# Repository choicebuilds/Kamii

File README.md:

# SumoBot v2
A significantly improved version of [SumoBot v1](https://github.com/choicebuilds/SumoBot-v1)!  Concise documentation intended as a project showcase for my portfolio/resume.
  
Notable Improvements:
- 4-layer PCB with dedicated 9V/5V planes and a solid ground plane to improve return current paths and help reduce EMI
- Decoupling & bulk capacitors placed throughout the board for improved power integrity
- STM32 MCU + STM32CubeMX + C/Cmake Firmware
- Various quality of life additions (e.g. strategy switch, remote start, on/off switch, etc.)
- Compact layout featuring 0402 surface-mount components (ft. dog-bone fanout for motor drivers for space and cost)
 
## Hardware Showcase

## Soldering Showcase
With the JLCPCB Stencil: $14.16 (PCB) + $21.69 (Shipping) - $5 (Coupon) = $30.85 + Tax  
Without the JLCPCB Stencil: $7 (PCB) + $3.12 (Shipping) - $5 (Coupon) = $5.12 + Tax  
I went with the second option and generated a stencil using the LPKF Protolaser.  
   
I would not recommend, especially for a small PCB, because the stencil did not sit flat. Required a few manual adjustments.  
  
Then, a reflow oven was used for SMD components:  
   
And the remaining components were through-hole soldered.

## WARNING
I flipped the polarity of the XT-30 connector on the silkscreen without reverse-polarity protection:  
  
It made a very loud sound when the bulk capacitor blew up. Lesson learned to always double check.

## Demo Video

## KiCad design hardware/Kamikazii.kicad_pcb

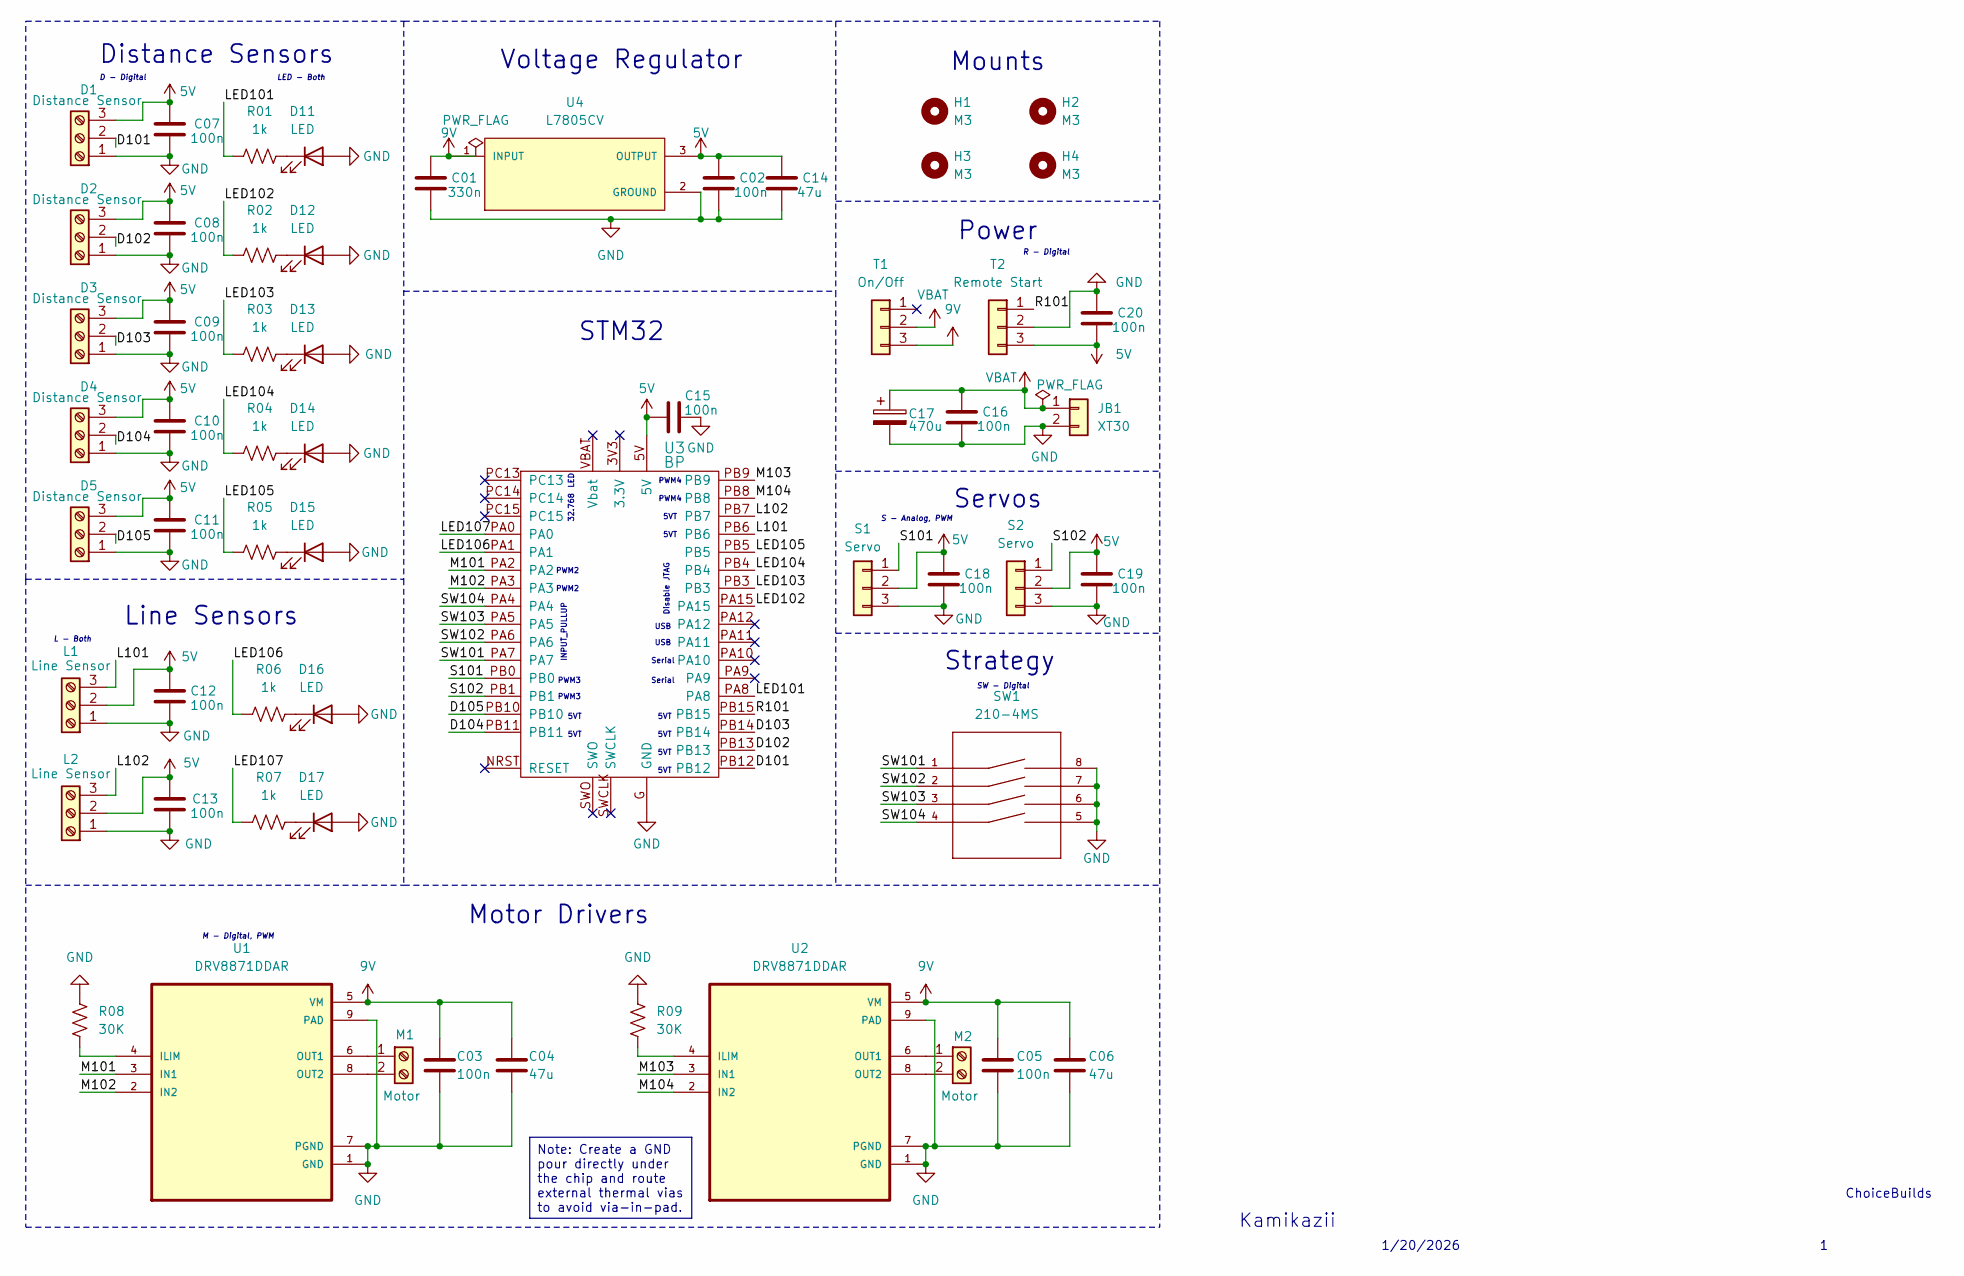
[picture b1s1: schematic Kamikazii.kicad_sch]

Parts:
C01: 330n; C_0402_1005Metric
C02, C03, C05, C07, C08, C09, C10, C11, C12, C13, C15, C16, C18, C19, C20: 100n; C_0402_1005Metric
C04, C06, C14: 47u; C_1210_3225Metric
C17: 470u; CP_Radial_D8.0mm_P3.50mm
D1, D2, D3, D4, D5: Distance Sensor; TerminalBlock_Xinya_XY308-2.54-3P_1x03_P2.54mm_Horizontal
D11, D12, D13, D14, D15, D16, D17: LED; LED_0402_1005Metric
H1, H2, H3, H4: M3; MountingHole_3.2mm_M3
JB1: XT30; AMASS_XT30U-F_1x02_P5.0mm_Vertical
L1, L2: Line Sensor; TerminalBlock_Xinya_XY308-2.54-3P_1x03_P2.54mm_Horizontal
M1, M2: Motor; TerminalBlock_Xinya_XY308-2.54-2P_1x02_P2.54mm_Horizontal
R01, R02, R03, R04, R05, R06, R07: 1k; R_0402_1005Metric
R08, R09: 30K; R_0402_1005Metric
S1, S2: Servo; PinHeader_1x03_P2.54mm_Vertical
SW1: 210-4MS; MANUFACTURER_PART_NUMBER 210-4MS
T1: On/Off; PinHeader_1x03_P2.54mm_Vertical
T2: Remote Start; PinHeader_1x03_P2.54mm_Vertical
U1, U2: DRV8871DDAR; VREG_LM5017MR_NOPB
U3: BP; blue_pill
U4: L7805CV; TO255P1040X460X1968-3; PARTREV 36

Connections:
5V: C02.2, C07.1, C08.1, C09.1, C10.1, C11.1, C12.1, C13.1, C14.2, C15.1, C18.2, C19.2, C20.1, D1.3, D2.3, D3.3, D4.3, D5.3, L1.2, L2.2, S1.2, S2.2, T2.3, U3.5V, U4.3 (OUTPUT)
9V: C01.2, C03.1, C04.1, C05.1, C06.1, T1.3, U1.5 (VM), U2.5 (VM), U4.1 (INPUT)
/D101: D1.2, U3.PB12
/D102: D2.2, U3.PB13
/D103: D3.2, U3.PB14
/D104: D4.2, U3.PB11
/D105: D5.2, U3.PB10
/L101: L1.3, U3.PB6
/L102: L2.3, U3.PB7
/LED101: R01.1, U3.PA8
/LED102: R02.1, U3.PA15
/LED103: R03.1, U3.PB3
/LED104: R04.1, U3.PB4
/LED105: R05.1, U3.PB5
/LED106: R06.1, U3.PA1
/LED107: R07.1, U3.PA0
/M101: U1.3 (IN1), U3.PA2
/M102: U1.2 (IN2), U3.PA3
/M103: U2.3 (IN1), U3.PB9
/M104: U2.2 (IN2), U3.PB8
/R101: T2.1, U3.PB15
/S101: S1.1, U3.PB0
/S102: S2.1, U3.PB1
/SW101: SW1.1, U3.PA7
/SW102: SW1.2, U3.PA6
/SW103: SW1.3, U3.PA5
/SW104: SW1.4, U3.PA4
GND: C01.1, C02.1, C03.2, C04.2, C05.2, C06.2, C07.2, C08.2, C09.2, C10.2, C11.2, C12.2, C13.2, C14.1, C15.2, C16.1, C17.2, C18.1, C19.1, C20.2, D1.1, D2.1, D3.1, D4.1, D5.1, D11.2 (A), D12.2 (A), D13.2 (A), D14.2 (A), D15.2 (A), D16.2 (A), D17.2 (A), JB1.2, L1.1, L2.1, R08.1, R09.1, S1.3, S2.3, SW1.5, SW1.6, SW1.7, SW1.8, T2.2, U1.1 (GND), U1.7 (PGND), U1.9 (PAD), U2.1 (GND), U2.7 (PGND), U2.9 (PAD), U3.G (GND), U4.2 (GROUND)
unnamed: D11.1 (K), R01.2
unnamed: D12.1 (K), R02.2
unnamed: D13.1 (K), R03.2
unnamed: D14.1 (K), R04.2
unnamed: D15.1 (K), R05.2
unnamed: D16.1 (K), R06.2
unnamed: D17.1 (K), R07.2
unnamed: M1.1, U1.6 (OUT1)
unnamed: M1.2, U1.8 (OUT2)
unnamed: M2.1, U2.6 (OUT1)
unnamed: M2.2, U2.8 (OUT2)
unnamed: R08.2, U1.4 (ILIM)
unnamed: R09.2, U2.4 (ILIM)
VBAT: C16.2, C17.1, JB1.1, T1.2

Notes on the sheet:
Power
Motor Drivers
INPUT_PULLUP
PWM3
32.768
5VT
PWM2
S - Analog, PWM
D - Digital
Kamikazii
L - Both
LED - Both
1/20/2026
Serial
PWM4
ChoiceBuilds
Mounts
SW - Digital
LED
R - Digital
Voltage Regulator
Servos
Line Sensors
Strategy
USB
Disable JTAG
STM32
Distance Sensors
M - Digital, PWM
Note: Create a GND pour directly under the chip and route external thermal vias to avoid via-in-pad.

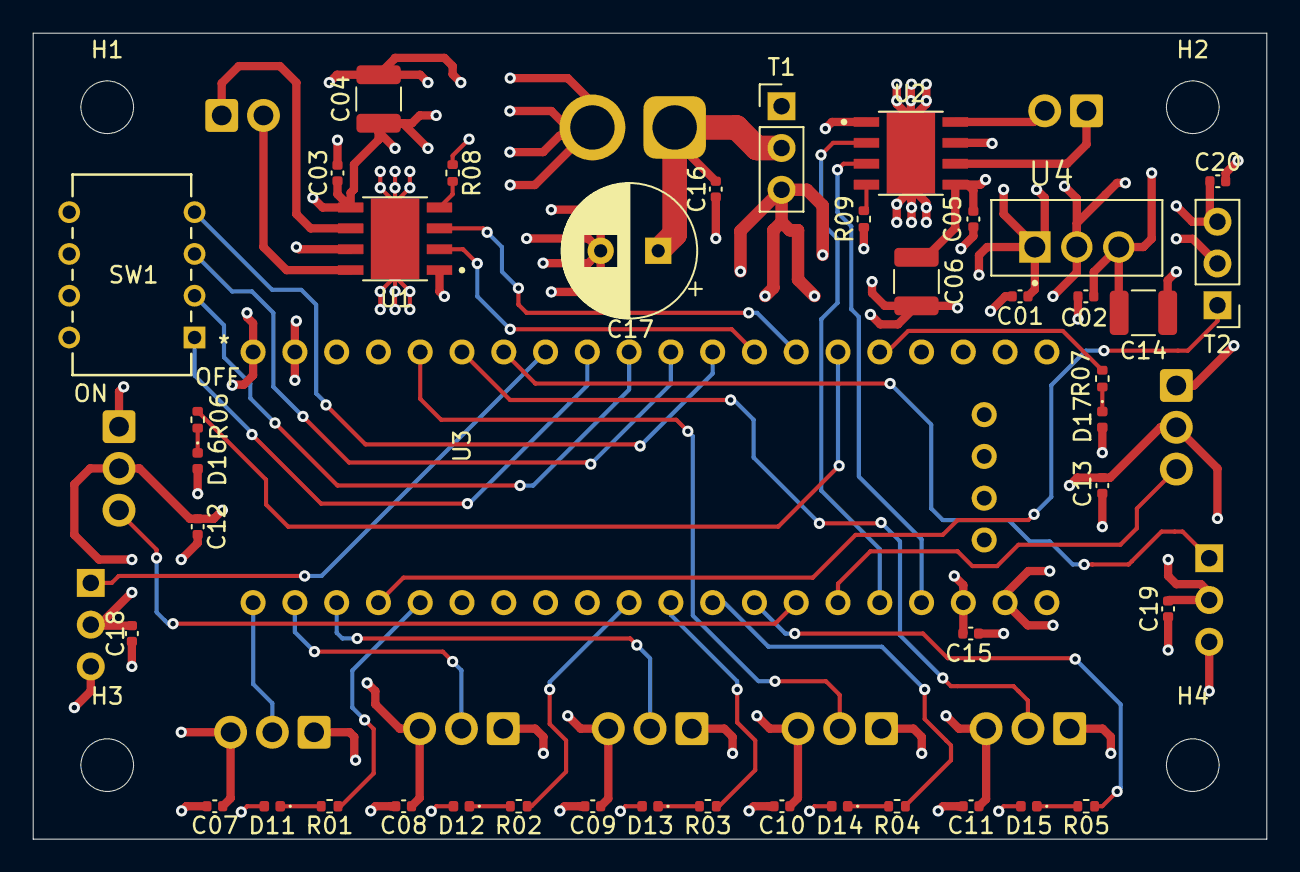
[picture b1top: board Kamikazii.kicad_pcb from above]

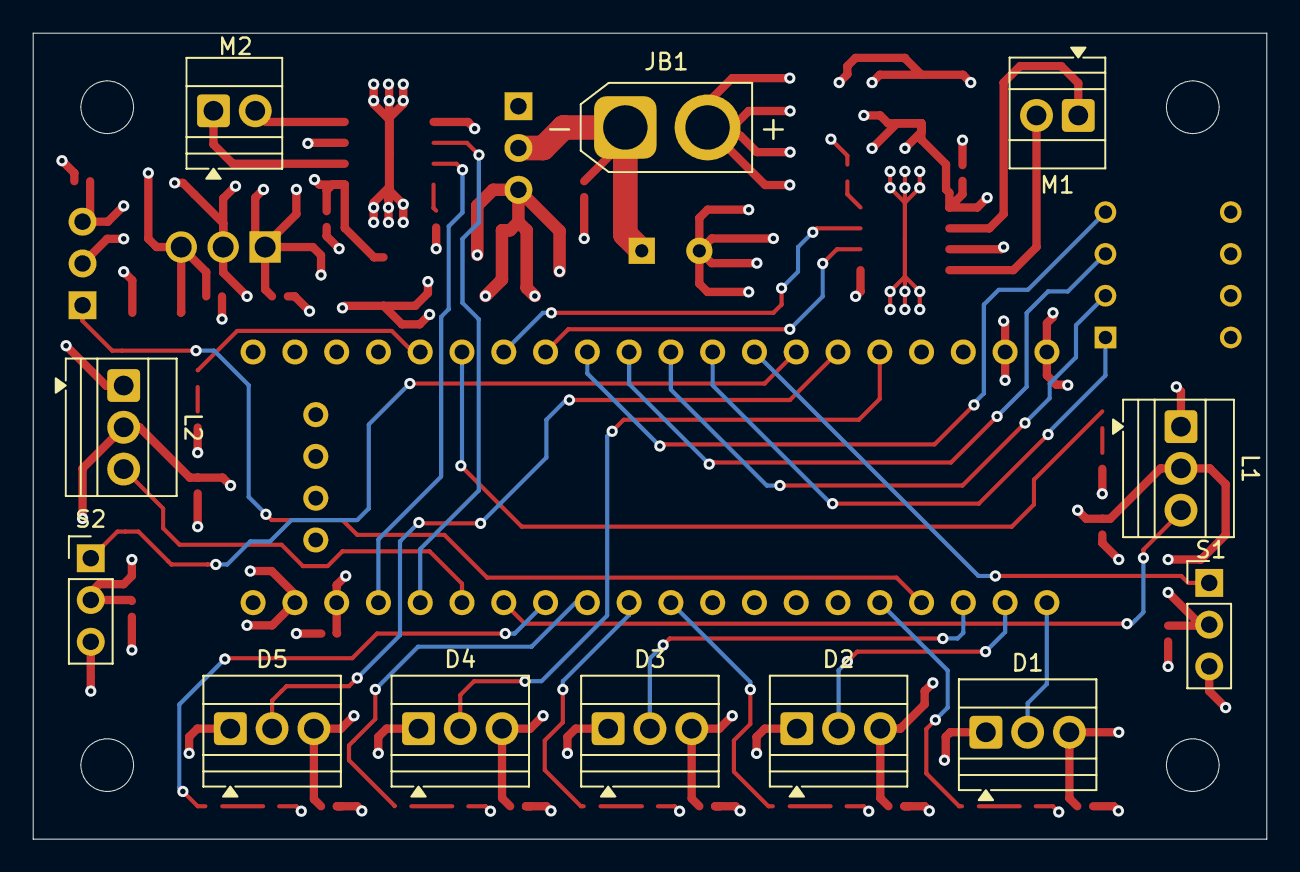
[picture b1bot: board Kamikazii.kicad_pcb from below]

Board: 4 copper layers, 75.0 x 49.0 mm, 59 parts (12 on the bottom side), 42 nets.

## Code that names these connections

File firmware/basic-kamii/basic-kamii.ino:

#define DS1 PB12
#define DS2 PB13
#define DS3 PB14
#define DS4 PB11
#define DS5 PB10
#define LS1 PB6
#define LS2 PB7
#define MA1 PA2
#define MA2 PA3
#define MB1 PB9
#define MB2 PB8
#define led1 PA8
#define led2 PA15
#define led3 PB3
#define led4 PB4
#define led5 PB5
#define led6 PA1
#define led7 PA0
#define SW1 PA4
#define SW2 PA5
#define SW3 PA6
#define SW4 PA7

int dv1;
int dv2;
int dv3;
int dv4;
int dv5;
int lv1;
int lv2;
int strategy;
int currentState;
int previousState;

//SETUP
int getStrategy() {
  int b0 = !digitalRead(SW1);
  int b1 = !digitalRead(SW2);
  int b2 = !digitalRead(SW3);
  int b3 = !digitalRead(SW4);
  return (b3 << 3) | (b2 << 2) | (b1 << 1) | b0;
}
enum States {
  IDLE,
  SEARCH,
  ATTACK
};

// MOVEMENT
void forwards() {
  analogWrite(MA1, 0);
  analogWrite(MA2, 50);
  analogWrite(MB1, 50);
  analogWrite(MB2, 0);
}
void backwards() {
  analogWrite(MA1, 50);
  analogWrite(MA2, 0);
  analogWrite(MB1, 0);
  analogWrite(MB2, 50);
}
void turnLeft () {
  analogWrite(MA1, 50);
  analogWrite(MA2, 0);
  analogWrite(MB1, 0);
  analogWrite(MB2, 0);
}
void turnRight() {
  analogWrite(MA1, 0);
  analogWrite(MA2, 0);
  analogWrite(MB1, 0);
  analogWrite(MB2, 50);
}
void brake() {
  analogWrite(MA1, 0);
  analogWrite(MA2, 0);
  analogWrite(MB1, 0);
  analogWrite(MB2, 0);
}
void charge() {
  analogWrite(MA1, 0);
  analogWrite(MA2, 255);
  analogWrite(MB1, 255);
  analogWrite(MB2, 0);
}

// HELPFUL
void getReadings() {
  dv1 = digitalRead(DS1);
  dv2 = digitalRead(DS2);
  dv3 = digitalRead(DS3);
  dv4 = digitalRead(DS4);
  dv5 = digitalRead(DS5);
  lv1 = digitalRead(LS1);
  lv2 = digitalRead(LS2);
}

void setup() {
  pinMode(DS1, INPUT);
  pinMode(DS2, INPUT);
  pinMode(DS3, INPUT);
  pinMode(DS4, INPUT);
  pinMode(DS5, INPUT);
  pinMode(LS1, INPUT);
  pinMode(LS2, INPUT);

  pinMode(SW1, INPUT_PULLUP);
  pinMode(SW2, INPUT_PULLUP);
  pinMode(SW3, INPUT_PULLUP);
  pinMode(SW4, INPUT_PULLUP);

  pinMode(led1, OUTPUT);
  pinMode(led2, OUTPUT);
  pinMode(led3, OUTPUT);
  pinMode(led4, OUTPUT);
  pinMode(led5, OUTPUT);
  pinMode(led6, OUTPUT);
  pinMode(led7, OUTPUT);

  pinMode(MA1, OUTPUT);
  pinMode(MA2, OUTPUT);
  pinMode(MB1, OUTPUT);
  pinMode(MB2, OUTPUT);

  strategy = getStrategy();
  currentState = ATTACK;
  digitalWrite(led2, LOW);
}

void loop() {
  switch(strategy) {
    case (0):
      switch (currentState) {
        case (ATTACK):
          forwards();
          delay(100);
          getReadings();
          while (dv3) {
            delay(100);
            getReadings();
          }
          currentState = SEARCH;
        case (SEARCH):
          brake();
          getReadings();
          if (dv1 || dv2) {
            turnLeft();
            getReadings();
            while (!dv3) {
              delay(100);
              getReadings();
            }
            brake();
            delay(100);
            currentState = ATTACK;
          }
          else if (dv4 || dv5) {
            turnRight();
            getReadings();
            while (!dv3) {
              delay(100);
              getReadings();
            }
            brake();
            delay(100);
            currentState = ATTACK;
          }
        }
    default:
      brake();
      delay(100000);
  }
}

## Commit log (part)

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2026-01-09 Dump Kamikazi files
2026-01-16 Add gitignore for DS_Store and Zone Identifiers
2026-01-16 Remove prexisting DS_Store files
2026-01-19 Add libraries for components
2026-01-19 Clean up files
2026-01-20 Finish schematic
2026-01-20 Add more capacitors and pass ERC
2026-01-21 Finalize schematic
2026-01-21 Start routing and fix minor schematic mistakes
2026-01-24 Make minor adjustments to schematic and finish layout with no errors
2026-01-24 Add pictures of PCB schematic, layouts, and 3D model
2026-01-24 Add pictures to README.md
2026-01-27 Add skeleton c files
2026-01-27 Make cmake run on an ARM compiler
2026-01-27 Add robot core
2026-01-27 Update gitignore for firmware files
2026-01-27 Clean up previously committed gitignore files
2026-03-19 Fiddle with cmake
2026-03-22 Add functional state machine

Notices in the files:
parts and their libraries:
COPYRIGHT: Copyright (C) 2024 Ultra Librarian. All rights reserved.
